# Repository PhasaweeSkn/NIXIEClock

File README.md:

# NIXIEClock  
 
 ## Conceptual Design

## Pin Assign

## Task (Planned)

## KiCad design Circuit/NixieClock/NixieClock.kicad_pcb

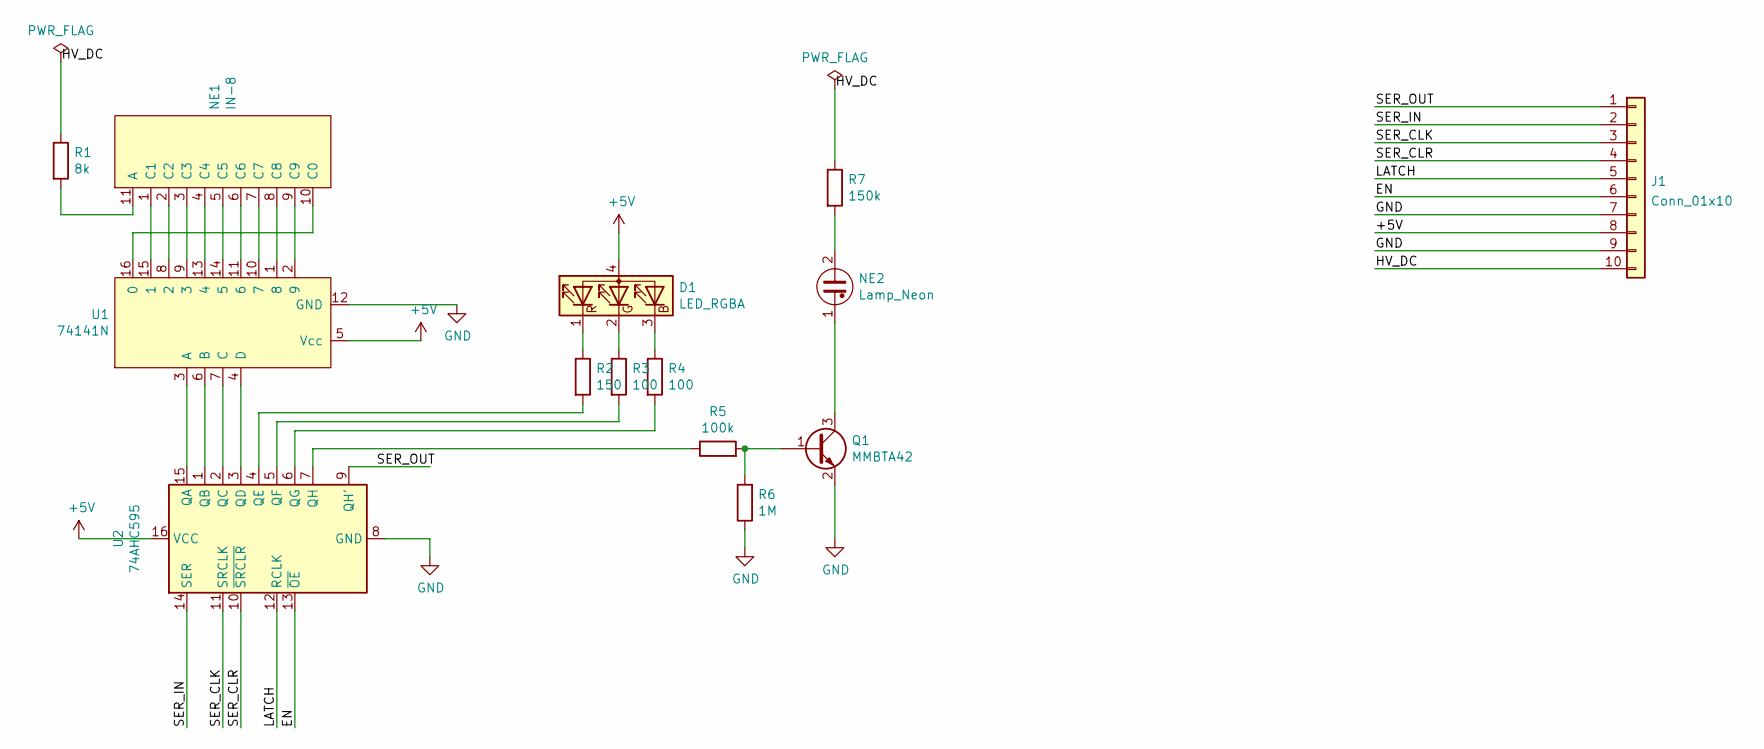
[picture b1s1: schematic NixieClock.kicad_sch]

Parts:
D1: LED_RGBA; LED_SK6805_PLCC4_2.4x2.7mm_P1.3mm
J1: Conn_01x10; JST_PH_B10B-PH-SM4-TB_1x10-1MP_P2.00mm_Vertical
NE1: IN-8
NE2: Lamp_Neon; R_Axial_DIN0204_L3.6mm_D1.6mm_P7.62mm_Horizontal
Q1: MMBTA42; SOT-23
R1: 8k; R_1206_3216Metric_Pad1.30x1.75mm_HandSolder
R2: 150; R_0603_1608Metric_Pad0.98x0.95mm_HandSolder
R3, R4: 100; R_0603_1608Metric_Pad0.98x0.95mm_HandSolder
R5: 100k; R_0805_2012Metric_Pad1.20x1.40mm_HandSolder
R6: 1M; R_0805_2012Metric_Pad1.20x1.40mm_HandSolder
R7: 150k; R_1206_3216Metric_Pad1.30x1.75mm_HandSolder
U1: 74141N; DIP-16_W7.62mm
U2: 74AHC595; SOIC-16_3.9x9.9mm_P1.27mm

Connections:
+5V: D1.4 (A), J1.8, U1.5 (Vcc), U2.16 (VCC)
/EN: J1.6, U2.13 (~OE)
/HV_DC: J1.10, R1.1, R7.1
/LATCH: J1.5, U2.12 (RCLK)
/SER_CLK: J1.3, U2.11 (SRCLK)
/SER_CLR: J1.4, U2.10 (~SRCLR)
/SER_IN: J1.2, U2.14 (SER)
/SER_OUT: J1.1, U2.9 (QH')
GND: J1.7, J1.9, Q1.2 (E), R6.1, U1.12 (GND), U2.8 (GND)
unnamed: D1.1 (RK), R2.1
unnamed: D1.2 (GK), R3.1
unnamed: D1.3 (BK), R4.1
unnamed: NE1.1 (C1), U1.15 (1)
unnamed: NE1.2 (C2), U1.8 (2)
unnamed: NE1.3 (C3), U1.9 (3)
unnamed: NE1.4 (C4), U1.13 (4)
unnamed: NE1.5 (C5), U1.14 (5)
unnamed: NE1.6 (C6), U1.11 (6)
unnamed: NE1.7 (C7), U1.10 (7)
unnamed: NE1.8 (C8), U1.1 (8)
unnamed: NE1.9 (C9), U1.2 (9)
unnamed: NE1.10 (C0), U1.16 (0)
unnamed: NE1.11 (A), R1.2
unnamed: NE2.1, Q1.3 (C)
unnamed: NE2.2, R7.2
unnamed: Q1.1 (B), R5.2, R6.2
unnamed: R2.2, U2.4 (QE)
unnamed: R3.2, U2.5 (QF)
unnamed: R4.2, U2.6 (QG)
unnamed: R5.1, U2.7 (QH)
unnamed: U1.3 (A), U2.15 (QA)
unnamed: U1.4 (D), U2.3 (QD)
unnamed: U1.6 (B), U2.1 (QB)
unnamed: U1.7 (C), U2.2 (QC)

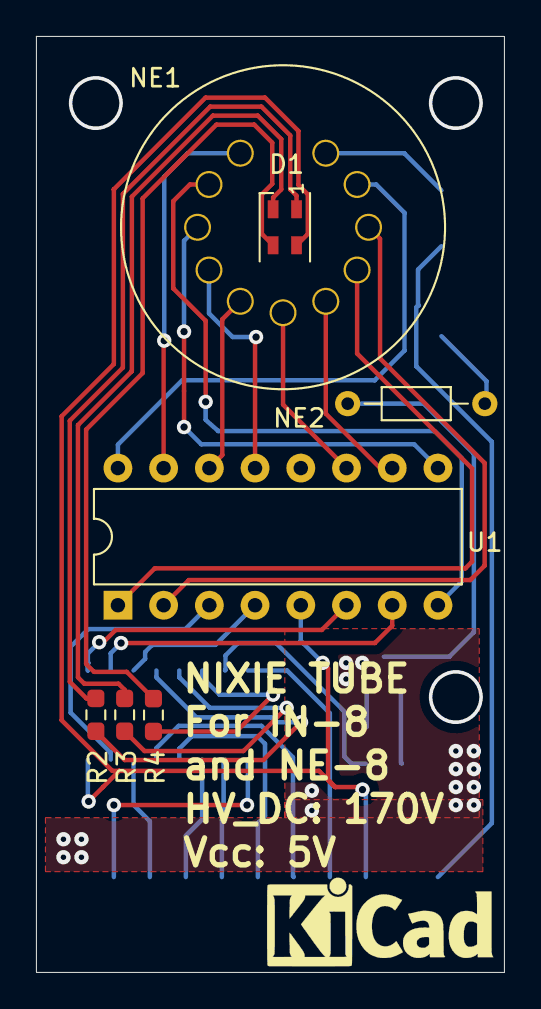
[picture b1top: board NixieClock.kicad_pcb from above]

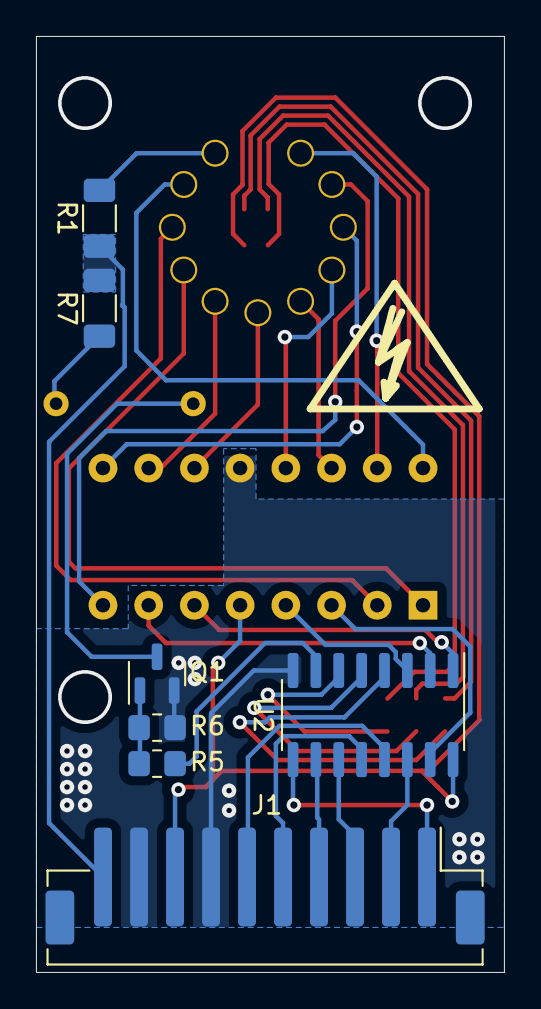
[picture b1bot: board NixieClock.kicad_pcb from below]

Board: 2 copper layers, 26.0 x 52.0 mm, 14 parts (7 on the bottom side), 34 nets.

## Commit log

2021-12-09 Update README.md
    Added Conceptual Design, Pin Assign, Task
2021-12-09 Code Skeleton Provisioning
2021-12-09 Clean Warning in code
2021-12-09 Added Platformio.ini to gitignore
2021-12-09 Added Skeleton of Circuit to Project
2021-12-09 Added IN-8 and 74141 to Library
2021-12-18 Place 74595 in Circuit
2021-12-18 Update web_page.cpp
    Add requirement
    SSID, Pass input
2021-12-20 Create HTML Page
    Add scan SSID name
    Add HTML Code
2021-12-23 Added Datasheet; Neon, Nixie, LED, BCD2DEC
2021-12-23 Added Calculate Sheet
2021-12-23 Added Neon, LED and miscellaneous
2022-01-08 Ignore Kicad Backup Files
2022-01-08 Added Datasheet HV Driver
2022-01-08 Migrate to Kicad6
2022-01-09 Set Conn Pin 4 as GND, Rule, and Board Shape
2022-01-11 Complete Route NIXIE tube to Driver
2022-01-13 Complete Route
2022-01-22 Generate Gerber File
